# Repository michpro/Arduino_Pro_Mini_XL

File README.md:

# **Arduino Pro Mini XL**

- [**Arduino Pro Mini XL**](#arduino-pro-mini-xl)
  - [**Overview**](#overview)
    - [**Features**](#features)
  - [**Schematic diagram**](#schematic-diagram)
  - [**Module visualisation**](#module-visualisation)
  - [**Assembly**](#assembly)
  - [**Production files**](#production-files)
  - [**Software Compatibility**](#software-compatibility)
    - [**Installing MightyCore**](#installing-mightycore)
  - [**Getting Started**](#getting-started)
    - [**Burning the Bootloader**](#burning-the-bootloader)
  - [**Troubleshooting**](#troubleshooting)
  - [**Physical Specifications**](#physical-specifications)
  - [**Reporting bugs**](#reporting-bugs)
  - [**Acknowledgments**](#acknowledgments)
  - [**License**](#license)
  - [**Support**](#support)

---

## **Overview**
The **Arduino Pro Mini XL** is a compact microcontroller board based on the **ATmega1284P**, designed to extend the capabilities of the standard Arduino Pro Mini while retaining its familiar form factor. With increased memory, additional I/O pins, and enhanced features, this board is well-suited for embedded applications requiring greater processing power and connectivity than the ATmega328P-based Arduino Pro Mini can provide. It integrates seamlessly with the Arduino ecosystem, making it accessible to hobbyists, engineers, and developers alike.

### **Features**
* **Microcontroller**: ATmega1284P
* **Flash Memory**: 128KB
* **SRAM**: 16KB
* **EEPROM**: 4KB
* **Digital I/O Pins**: 22
* **Analog Input Pins**: 2
* **Analog Comparator**: 1
* **PWM Channels**: 8
* **UARTs**: 2
* **SPI**: 1
* **I2C**: 1
* **Operating Voltage**: 5V
* **Clock Speed**: 20/16/8MHz
* **Form Factor**: Compatible with Arduino Pro Mini

---

## **Schematic diagram**

## **Module visualisation**
(click on the image to see the 3D model)
<p align="center"></p>

## **Assembly**
[Interactive BOM and placement](https://michpro.github.io/Arduino_Pro_Mini_XL/ibom.html)

## **Production files**
Production files can be found [**here**](./production/).

---

## **Software Compatibility**

The Arduino Pro Mini XL is supported by the Arduino IDE through the [**MightyCore**](https://github.com/MCUdude/MightyCore) board package, which provides board definitions for the ATmega1284P.

### **Installing MightyCore**

To configure the Arduino IDE:

1. Open the Arduino IDE.
2. Navigate to `File` > `Preferences`.
3. Add the following URL to the `Additional Boards Manager URLs` field:  
   ```
   https://mcudude.github.io/MightyCore/package_MCUdude_MightyCore_index.json
   ```
4. Click `OK`.
5. Go to `Tools` > `Board` > `Boards Manager`.
6. Search for "MightyCore" and install the package.

After installation, select **"ATmega1284P"** under `Tools` > `Board`, and configure the variant and clock settings as needed.

## **Getting Started**

1. **Connect the Board**: Attach an FTDI-compatible cable or adapter to the 6-pin programming header.
2. **Configure the IDE**: Select the ATmega1284P board and the appropriate serial port in the Arduino IDE.
3. **Upload a Sketch**: Use a simple sketch, such as "Blink," to test functionality.
   ```cpp
   void setup()
   {
      pinMode(PIN_PC6, OUTPUT); // Onboard LED 
                                // Don't forget to close JP1.
   }

   void loop()
   {
      digitalWrite(PIN_PC6, HIGH);
      delay(1000);
      digitalWrite(PIN_PC6, LOW);
      delay(1000);
   }
   ```
4. **Verify Operation**: Confirm that the onboard LED blinks, indicating successful setup. **Don't forget to close JP1.**

### **Burning the Bootloader**

To burn the bootloader using an ISP programmer:

1. Connect the ISP programmer to the board’s pins.
2. In the Arduino IDE, select the ATmega1284P board and your programmer.
3. Choose `Tools` > `Burn Bootloader`.

Consult the MightyCore documentation for correct fuse settings.

## **Troubleshooting**

- **Upload Failures**: Verify board and port settings; check FTDI connections and drivers.
- **Power Issues**: Ensure input voltage is 5V (VCC); inspect for shorts. *Board has no RAW input*
- **Pin Mapping**: Confirm pin assignments, as they differ from the ATmega328P.

## **Physical Specifications**

- **Dimensions**: Comparable to the Arduino Pro Mini (18.5mm x 33mm).

---

## **Reporting bugs**

[Create an issue on GitHub](https://github.com/michpro/Arduino_Pro_Mini_XL/issues)

---

## **Acknowledgments**

Thanks to the Arduino community and the [**MightyCore**](https://github.com/MCUdude/MightyCore) developers for enabling support for the ATmega1284P.

---

## **License**
Copyright © 2020-2025 Michal Protasowicki

This project is released under CERN Open Hardware Licence Version 2 - Permissive.

---

## **Support**
If You find my projects interesting and You wanted to support my work, You can give me a cup of coffee or a keg of beer :)

&nbsp;&nbsp;&nbsp;&nbsp;&nbsp;&nbsp;&nbsp;&nbsp;&nbsp;&nbsp;

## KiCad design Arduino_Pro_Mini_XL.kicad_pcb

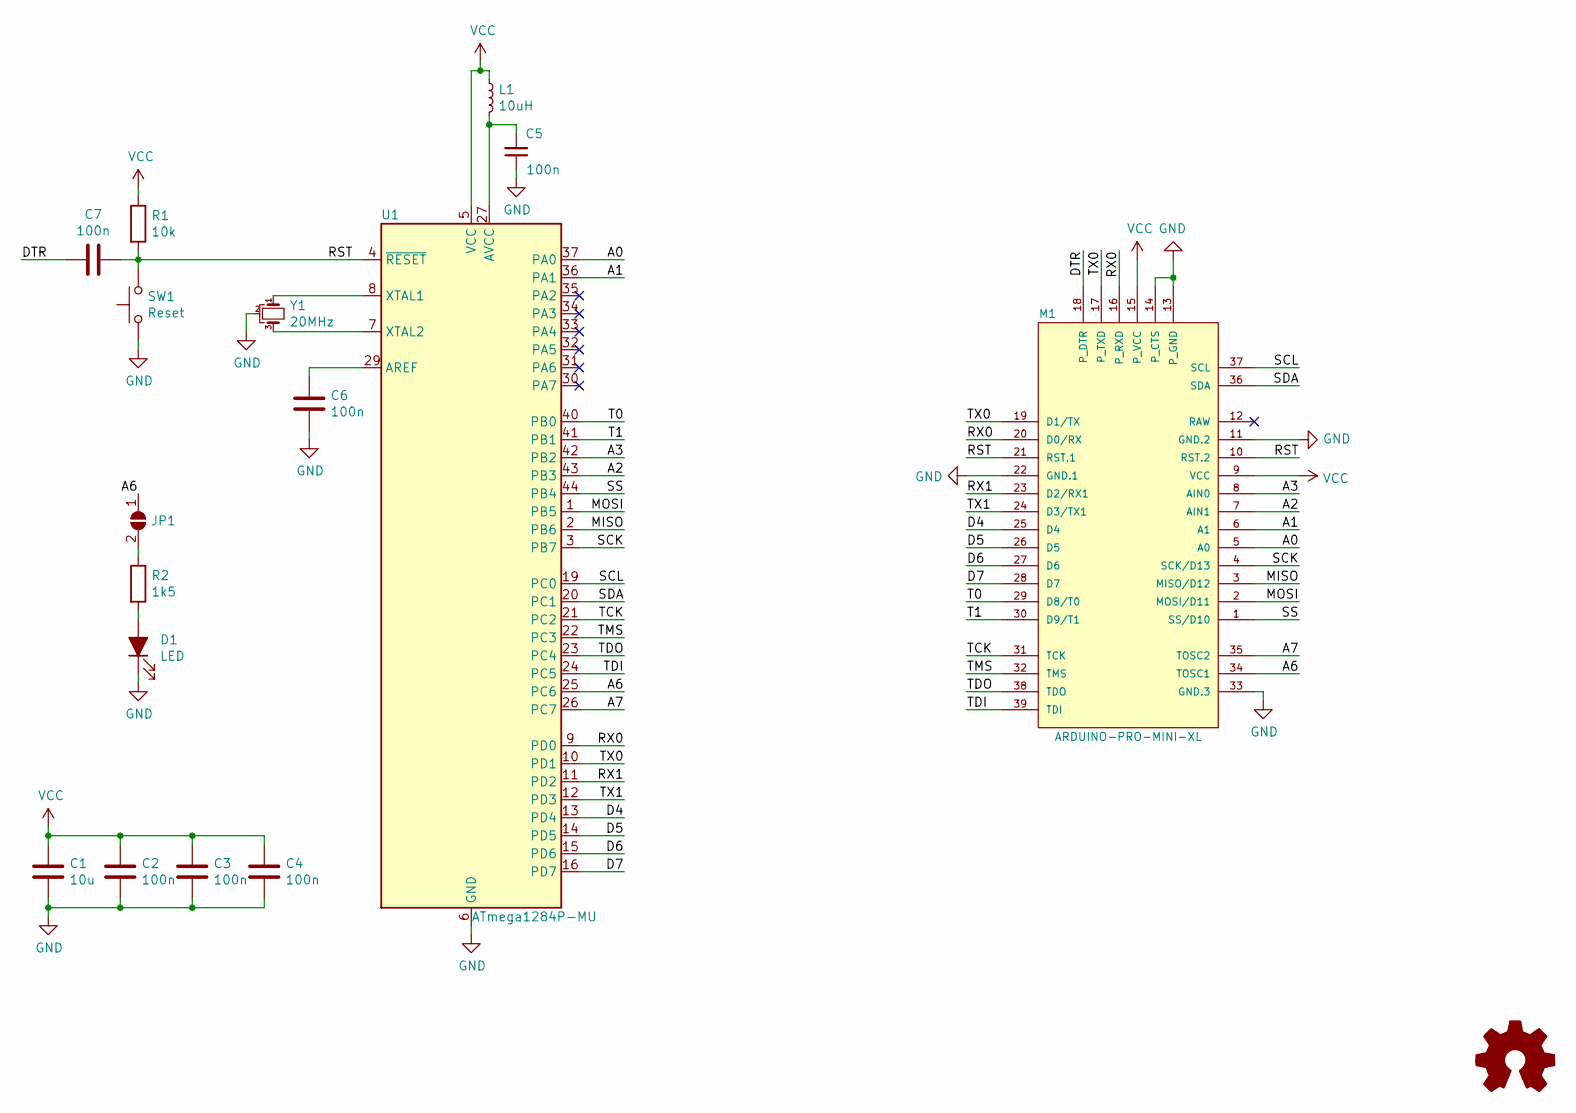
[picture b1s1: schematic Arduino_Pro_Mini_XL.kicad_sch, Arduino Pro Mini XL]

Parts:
C1: 10u; C_0603_1608Metric; LCSC C19702
C2, C3, C4, C6, C7: 100n; C_0603_1608Metric; LCSC C14663
C5: 100n; C_0805_2012Metric; LCSC C49678
D1: LED; LED_0805_2012Metric; LCSC C2297
JP1: SolderJumper_2_Open; SolderJumper-2_P1.3mm_Open_TrianglePad1.0x1.5mm
L1: 10uH; L_0805_2012Metric; LCSC C1046
LOGO1: Logo_Open_Hardware_Small
M1: ARDUINO-PRO-MINI-XL; diy-modules-ARDUINO-PRO-MINI-XL-BRD
R1: 10k; R_0603_1608Metric; LCSC C25804
R2: 1k5; R_0603_1608Metric; LCSC C22843
SW1: Reset; SW_SPST_EVQPE1; LCSC C455280
U1: ATmega1284P-MU; QFN-44-1EP_7x7mm_P0.5mm_EP5.2x5.2mm; LCSC C1337217
Y1: 20MHz; muRata-resonator_SMD_CSTCExxM00G55-R0; LCSC C2650766

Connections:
/A0: M1.5 (A0), U1.37 (PA0)
/A1: M1.6 (A1), U1.36 (PA1)
/A2: M1.7 (AIN1), U1.43 (PB3)
/A3: M1.8 (AIN0), U1.42 (PB2)
/A6: JP1.1 (A), M1.34 (TOSC1), U1.25 (PC6)
/A7: M1.35 (TOSC2), U1.26 (PC7)
/D4: M1.25 (D4), U1.13 (PD4)
/D5: M1.26 (D5), U1.14 (PD5)
/D6: M1.27 (D6), U1.15 (PD6)
/D7: M1.28 (D7), U1.16 (PD7)
/DTR: C7.2, M1.18 (P_DTR)
/MISO: M1.3 (MISO/D12), U1.2 (PB6)
/MOSI: M1.2 (MOSI/D11), U1.1 (PB5)
/RST: C7.1, M1.10 (RST.2), M1.21 (RST.1), R1.2, SW1.1, U1.4 (~RESET)
/RX0: M1.16 (P_RXD), M1.20 (D0/RX), U1.9 (PD0)
/RX1: M1.23 (D2/RX1), U1.11 (PD2)
/SCK: M1.4 (SCK/D13), U1.3 (PB7)
/SCL: M1.37 (SCL), U1.19 (PC0)
/SDA: M1.36 (SDA), U1.20 (PC1)
/SS: M1.1 (SS/D10), U1.44 (PB4)
/T0: M1.29 (D8/T0), U1.40 (PB0)
/T1: M1.30 (D9/T1), U1.41 (PB1)
/TCK: M1.31 (TCK), U1.21 (PC2)
/TDI: M1.39 (TDI), U1.24 (PC5)
/TDO: M1.38 (TDO), U1.23 (PC4)
/TMS: M1.32 (TMS), U1.22 (PC3)
/TX0: M1.17 (P_TXD), M1.19 (D1/TX), U1.10 (PD1)
/TX1: M1.24 (D3/TX1), U1.12 (PD3)
GND: C1.2, C2.2, C3.2, C4.2, C5.1, C6.2, D1.1 (K), M1.11 (GND.2), M1.13 (P_GND), M1.14 (P_CTS), M1.22 (GND.1), M1.33 (GND.3), SW1.2, U1.6 (GND), U1.18 (GND), U1.28 (GND), U1.39 (GND), U1.45 (GND), Y1.2
unnamed: D1.2 (A), R2.2
unnamed: JP1.2 (B), R2.1
unnamed: C6.1, U1.29 (AREF)
unnamed: C5.2, L1.2, U1.27 (AVCC)
unnamed: U1.8 (XTAL1), Y1.1
unnamed: U1.7 (XTAL2), Y1.3
VCC: C1.1, C2.1, C3.1, C4.1, L1.1, M1.9 (VCC), M1.15 (P_VCC), R1.1, U1.5 (VCC), U1.17 (VCC), U1.38 (VCC)

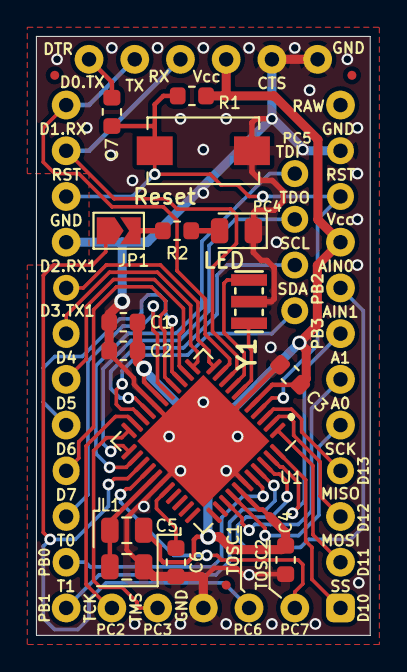
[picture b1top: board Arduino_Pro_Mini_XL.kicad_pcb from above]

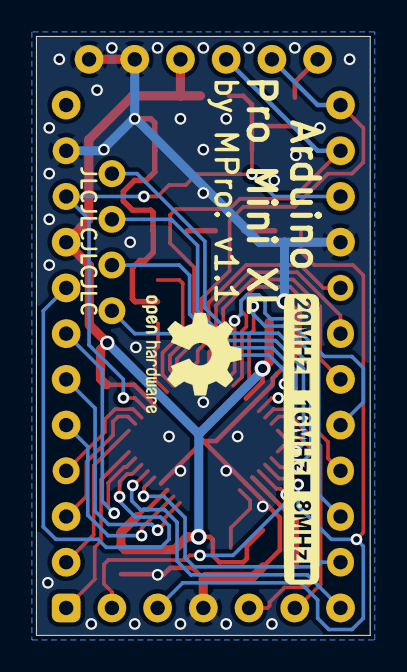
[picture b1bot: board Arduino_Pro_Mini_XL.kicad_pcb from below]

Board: 2 copper layers, 18.5 x 33.3 mm, 21 parts (2 on the bottom side), 36 nets.

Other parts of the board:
REF1, REF2, REF3: Fiducial_0.5mm_Mask1mm
REF4: OSHW-Logo2_7.3x6mm_SilkScreen
REF5: LOGO; Logo_FREQ_20_16_8MHz

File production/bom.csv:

Designator,Footprint,Quantity,Value,LCSC Part #
C1,0603,1,10u,C19702
"C2, C3, C4, C6, C7",0603,5,100n,C14663
C5,0805,1,100n,C49678
D1,0805,1,LED,C2297
L1,0805,1,10uH,C1046
R1,0603,1,10k,C25804
R2,0603,1,1k5,C22843
SW1,SW_SPST_EVQPE1,1,Reset,C455280
U1,QFN-44-1EP_7x7mm_P0.5mm_EP5.2x5.2mm,1,ATmega1284P-MU,C1337217
Y1,muRata-resonator_SMD_CSTCExxM00G55-R0,1,20MHz,C2650766

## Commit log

2023-08-30 board version 1.1 updated to KiCad 7.x format
2025-04-06 project files updated to Kicad version 9.0.1
2025-08-07 documentation updated

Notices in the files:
Arduino_Pro_Mini_XL.kicad_pcb:
© 2020-2023 MPro
Licensed under CERN-OHL-P v2 or any later version
